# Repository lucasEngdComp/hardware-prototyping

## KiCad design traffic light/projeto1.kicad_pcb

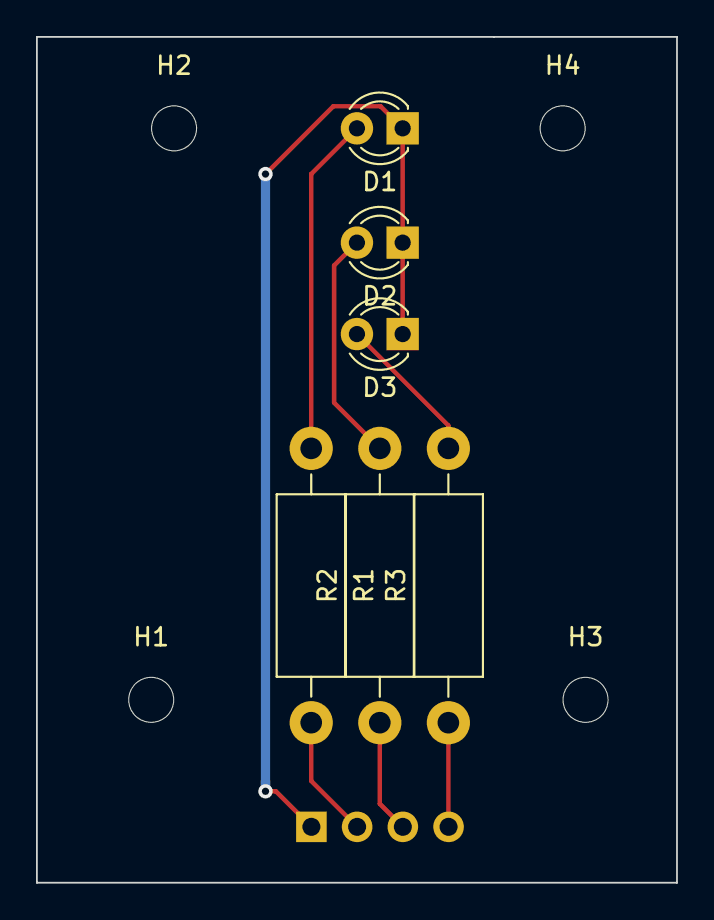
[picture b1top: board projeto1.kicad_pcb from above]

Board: 2 copper layers, 35.6 x 47.0 mm, 11 parts (1 on the bottom side), 7 nets.

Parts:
D1, D2, D3: LED; LED_D3.0mm
H1, H2, H3, H4: MountingHole; MountingHole_2.5mm
J1: Conn_01x04_Male; PinHeader_1x04_P2.54mm_Horizontal
R1, R2, R3: R; R_Axial_DIN0411_L9.9mm_D3.6mm_P15.24mm_Horizontal

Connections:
GND: D1.1 (K), D2.1 (K), D3.1 (K), J1.1
unnamed: D1.2 (A), R1.1
unnamed: D3.2 (A), R3.2
unnamed: J1.4, R3.1
unnamed: J1.2, R1.2
unnamed: J1.3, R2.1
unnamed: D2.2 (A), R2.2

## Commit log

2022-05-04 Design a Traffic light PCB using kicad6.
2022-05-06 project using Kicad6
